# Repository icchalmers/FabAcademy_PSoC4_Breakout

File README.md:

# FabAcademy_PSoC4_Breakout

A small breakout board for the PSoC 4 CY8CKIT-049 42xx prototyping kit. It includes WS2812b LEDs, a TMP275 temperature sensor, CapSense buttons and a header to attach an ESP-01 module. It was made as part [Fab Academy 2015](http://www.fabacademy.org/) at [Fab Lab Strathclyde](http://www.strath.ac.uk/fablab/). You can follow the process on [my class website](http://fabacademy.org/archives/2015/eu/students/chalmers.iain/index.html). The content is also mirrored to [my GitHub Pages site](http://icchalmers.github.io/).

Note that there is one jumper wire needed if making this as a single sided board.

# WARNING!

This board runs at 3.3V. You MUST modify the USB-UART board that comes with the kit or bad things will happen! The simplest option is to remove the fuse on VUSB and power everything from the board. More options are discussed on my class webpage.

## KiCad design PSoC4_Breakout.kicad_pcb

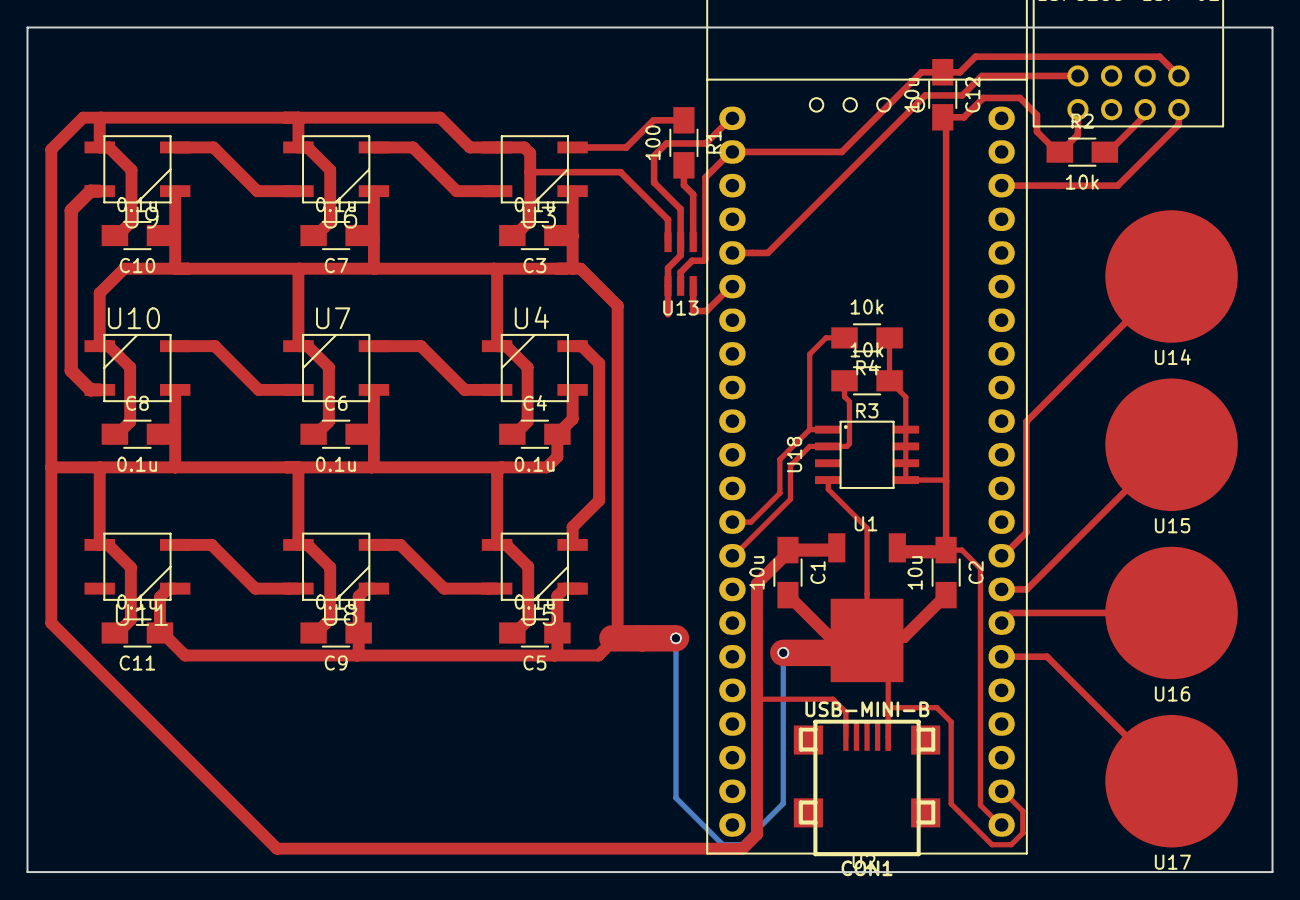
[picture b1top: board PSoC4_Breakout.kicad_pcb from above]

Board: 2 copper layers, 94.0 x 63.8 mm, 35 parts (0 on the bottom side), 25 nets.

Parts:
C1, C2, C12: 10u; C_1206_HandSoldering_IainEdit
C3, C4, C5, C6, C7, C8, C9, C10, C11: 0.1u; C_1206_HandSoldering_IainEdit
CON1: USB-MINI-B; conn_usb_B_mini_smd
R1: 100; C_1206_HandSoldering_IainEdit
R2, R3, R4: 10k; C_1206_HandSoldering_IainEdit
U1: LP38691; LP38691_TO252_handsolder
U2: CY8CKIT-049-42xx; CYKIT-49-42xx
U3, U4, U5, U6, U7, U8, U9, U10, U11: WS2812b; WS2812b_handsolder
U12: ESP8266-ESP-01
U13: SN74LVC1T45; TI-DBV-SOT23_handsolder
U14, U15, U16, U17: CapSenseButton
U18: TMP275; TI-D-SO-8_handsolder

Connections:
+5V: C1.1, C3.2, C4.2, C5.2, C6.2, C7.2, C8.2, C9.2, C10.2, C11.2, CON1.1, U1.1, U3.1, U4.1, U5.1, U6.1, U7.1, U8.1, U9.1, U10.1, U11.1, U13.6
GND: C1.2, C2.2, C3.1, C4.1, C5.1, C6.1, C7.1, C8.1, C9.1, C10.1, C11.1, CON1.5, U1.tab, U2.24, U3.3, U4.3, U5.3, U6.3, U7.3, U8.3, U9.3, U10.3, U11.3, U18.4
unnamed: C12.1, U2.21, U12.2, U13.2
unnamed: R1.1, U3.4
unnamed: R1.2, U13.4
unnamed: R2.2, U12.3
unnamed: U3.2, U6.4
unnamed: U4.2, U5.4
unnamed: U4.4, U7.2
unnamed: U5.2, U8.4
unnamed: U6.2, U9.4
unnamed: U7.4, U10.2
unnamed: U9.2, U10.4
unnamed: U8.2, U11.4
unnamed: U2.42, U12.1
unnamed: U2.18, U12.8
unnamed: U2.22, U13.1, U13.5
unnamed: U2.17, U13.3
unnamed: U2.31, U14.1
unnamed: U2.30, U15.1
unnamed: U2.29, U16.1
unnamed: U2.28, U17.1
SCL: R3.2, U2.9, U18.2
SDA: R4.2, U2.10, U18.1
VDD: C2.1, C12.2, R2.1, R3.1, R4.1, U1.3, U2.23, U12.7, U18.5, U18.6, U18.7, U18.8

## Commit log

2015-03-24 Initial upload
2015-05-16 Fix typo
